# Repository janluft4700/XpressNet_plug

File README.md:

# XpressNet_plug

Based on https://www.opendcc.de/elektronik/xpressnet/plug_e.html
Different layout of PCB

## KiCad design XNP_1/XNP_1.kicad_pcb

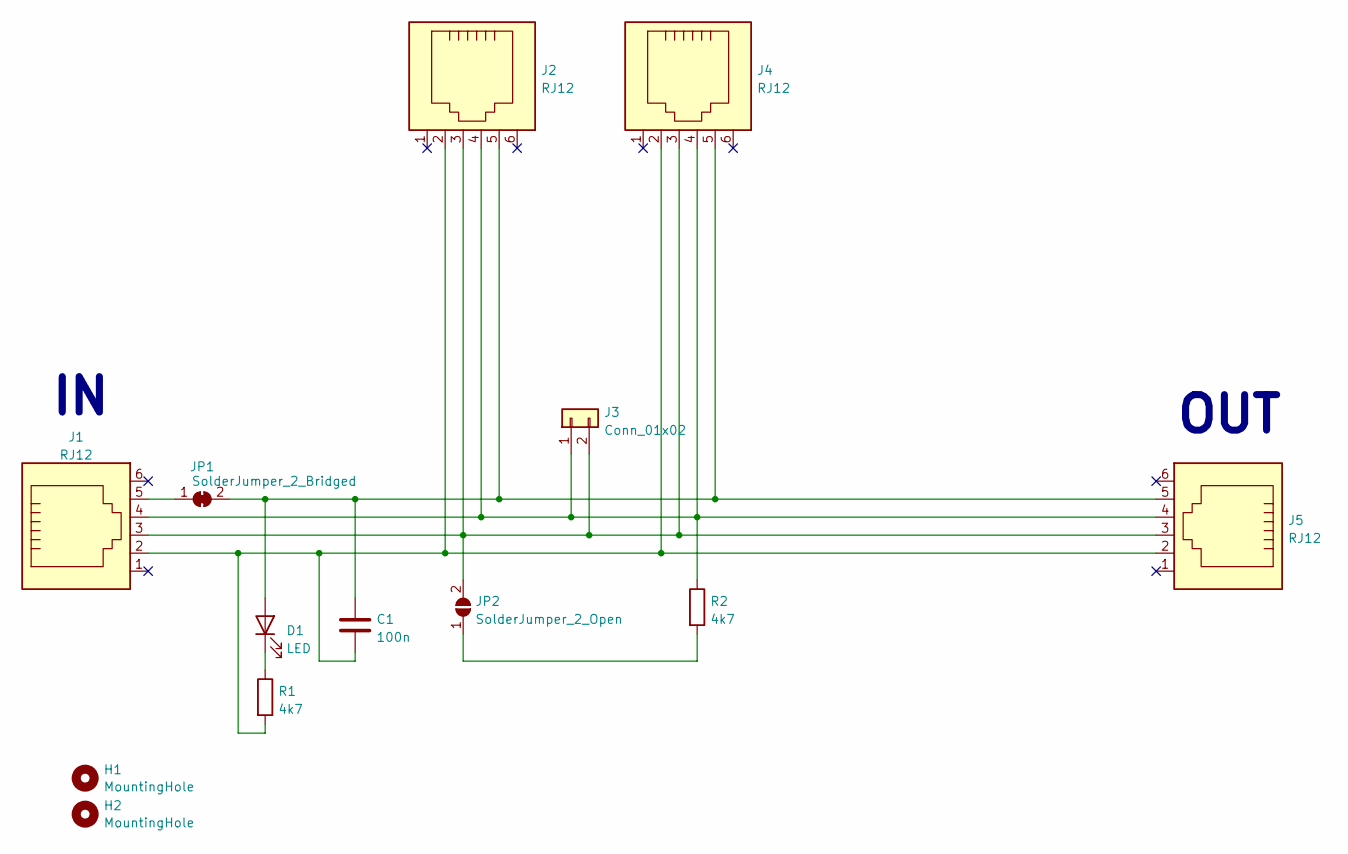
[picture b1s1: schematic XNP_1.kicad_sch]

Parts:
C1: 100n; C_0805_2012Metric
D1: LED; LED_D3.0mm_Clear
H1, H2: MountingHole; MountingHole_3mm_Pad_TopBottom
J1, J2, J4, J5: RJ12; RJ12_Amphenol_54601
J3: Conn_01x02; PinSocket_1x02_P2.54mm_Vertical
JP1: SolderJumper_2_Bridged; SolderJumper-2_P1.3mm_Bridged_RoundedPad1.0x1.5mm
JP2: SolderJumper_2_Open; SolderJumper-2_P1.3mm_Open_RoundedPad1.0x1.5mm
R1, R2: 4k7; R_0805_2012Metric

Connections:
unnamed: C1.2, J1.2, J2.2, J4.2, J5.2, R1.2
unnamed: C1.1, D1.2 (A), J2.5, J4.5, J5.5, JP1.2 (B)
unnamed: D1.1 (K), R1.1
unnamed: J1.4, J2.4, J3.1, J4.4, J5.4, R2.1
unnamed: J1.3, J2.3, J3.2, J4.3, J5.3, JP2.2 (B)
unnamed: J1.5, JP1.1 (A)
unnamed: JP2.1 (A), R2.2

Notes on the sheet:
OUT

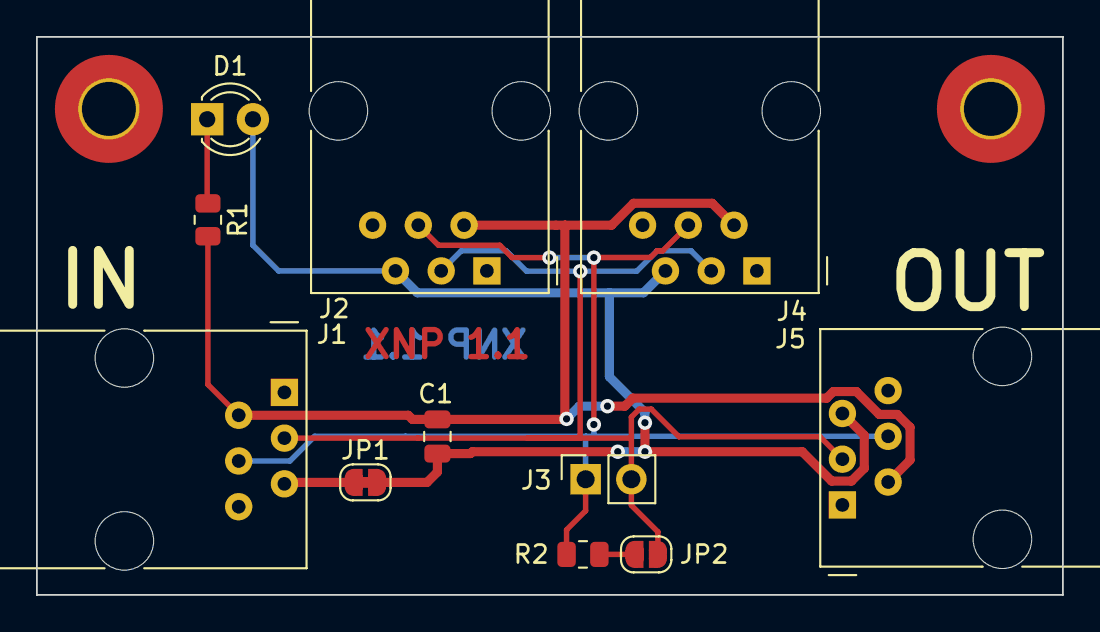
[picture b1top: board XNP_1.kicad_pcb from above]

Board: 2 copper layers, 57.0 x 31.0 mm, 13 parts (0 on the bottom side), 7 nets.

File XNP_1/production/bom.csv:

Designator,Footprint,Quantity,Value,LCSC Part #
C1,0805,1,100n,
D1,LED_D3.0mm_Clear,1,LED,
"H1, H2",MountingHole_3mm_Pad_TopBottom,2,MountingHole,
"J1, J2, J4, J5",RJ12_Amphenol_54601,4,RJ12,
J3,PinSocket_1x02_P2.54mm_Vertical,1,Conn_01x02,
JP1,SolderJumper-2_P1.3mm_Bridged_RoundedPad1.0x1.5mm,1,SolderJumper_2_Bridged,
JP2,SolderJumper-2_P1.3mm_Open_RoundedPad1.0x1.5mm,1,SolderJumper_2_Open,
"R1, R2",0805,2,4k7,

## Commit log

2025-08-15 Založení projektu
2025-08-15 git ignore
2025-08-15 Rozložení na DPS
2025-08-15 Dokončen návrh DPS
2025-08-21 Výrobní data
